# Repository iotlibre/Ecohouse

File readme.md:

# EcoHouse

Este kit de medida está pensado para tomar las medidas de consumo eléctrico de una vivienda o de un edificio con consumos inferiores a 10 KW. El sistema permite diferenciar varias zonas.

EcoHouse se puede instalar en el cuadro eléctrico principal o en cualquier otra parte  que nos permita tomar datos del consumo mediante pinzas (transformadores de intensidad). 

En el un edificio podemos tener tantos dispositivos como sean necesarios y el servidor EcoEficiencia los integrará en la misma instalación sin necesidad de configuraciones adicionales o cambios en el Firmware.

La comunicación se hace mediante Wifi por lo que no es necesario el cableado de datos al equipo solamente es necesario que esté dentro de la cobertura de la red WIFI del edificio. 

Para su uso no son necesarios conocimientos de informática aunque todos los desarrollos y el hardware están hechos bajo licencias libres lo que permite la modificación y mejora de las funcionalidades.

## Listado con las principales características
Las principales características de EcoBuilding son:
- 6 entradas para sensores de corriente con salida estandar de 50 mA o 1 Voltio
- Comunicación a Internet por WIFI local
- Configurable vía Web
- Display para mostrar el consumo instantáneo
- Alimentación a 220 voltios de corriente alterna
- Montaje en carril din
- Es posible configurar dos entradas analógicas adicionales pero en este caso el display permanecerá inoperativo
- La PCB integra un Arduino nano  con el ESP8266 12E
- Compatible con el [servidor de Open Energy Monitor](https://emoncms.org/)

## Montaje
El listado de componentes que has debido recibir es el siguientes:

- 1 PCB con los componentes de superficie ya montados
- 1 Carcasa para carril DIN
- 1 Tapa superior carcasa con display LCD 1602 y adaptador IIC/I2C
- 1 PCB Mesh building
- 1 Fuente de alimentación a 12 voltios
- 1 Arduino Nano
- 1 Integrado ESP8266 12E con el firmware mesh_building incluido
- 1 Convertidor DC-DC Step Down ajustable (salida 7,5V)
- 1 Regulador de tensión LM 1117
- 2 Conectores macho -hembra de 2.0mm para el ESP
- 2 Conectores macho hembra de 2.54mm para Arduino
- 2 Conectores macho hembra de 2.54mm para al display
- 9 Terminales de tornillo para PCB
- 2 Resistencias 10k 
- 3 Condensador 22uF
- 1 Condensador de 100nF
- 1 Diodo 1N4007

## Montaje
Partiendo de la PCB con los componentes de superficie soldar los componentes de menor a mayor tamaño por este orden:
- Resistencias
- Diodos
- Convertidor DC-DC Step Down ajustable (salida 7,5V)
- Conectores macho hembra de 2.0mm para el ESP
- Conectores macho hembra de 2.54mm para Arduino
- Conectores macho hembra de 2.54mm para al display
- Terminales de tornillo para PCB
- Condensador 22uF
- Condensador de 100nF
- Regulador de tensión LM 1117
 
Una vez esta completa la PCB insertar los integrados en sus posiciones
- Integrado ESP8266 12E
- Arduino Nano

Mirar la imagen para colocar los integrados de forma correcta, de otra maner no funcionarán y pueden sufrir daños

Por último conectar la tapa superior con el display a la PCB y montar la carcasa.

## Puesta a punto
La puesta a punto de libre_building consta de dos partes:
- El ajuste del voltaje de trabajo
- La configuración en la instalación

### El ajuste del voltaje de trabajo
El ajuste del voltaje de trabajo se hace para adaptar cualquier alimentación al voltaje de trabajo de EcoHouse que es 7,5 voltios.

La fuente de alimentación suministrada es de 12 voltios aunque el dispositivo funciona correctamente siempre que el voltaje de trabajo quede configurado entre 7 y 9 voltios.

Una vez conectada la  fuente de alimentación medir el voltaje en el punto (W103), situado al lado de  el Convertidor DC-DC (U1), y ajustarlo a 7,5 voltios con el potenciómetro que incorpora el convertidor. 

### La configuración en la instalación
En este punto se definen los parámetros del servidor de destino y la wifi local a la que va a estar conectado el dispositivo. Con este fin, la primera vez que se ponga en servicio el ESP y siempre que no encuentre la WIFI configurada, el ESP 8266 12E creará su propio punto de acceso, su propia red WIFI . Conectandose a cualquier dirección a través de este punto de acceso nos aparecerá la página de configuración del ESP. Tengase en cuenta que una  vez configurado el ESP y conectado a una red WIFI el router le asignará una única dirección IP a la que será necesario acceder para cambiar la configuración.

En caso de que se quiera actualizar el firmware del ESP a la última versión, este se puede encontrar en: [ecohouse-emonESP ](https://github.com/iotlibre/Ecohouse/tree/master/EmonESP)

### El firmware de Arduino
El firmware que que esta cargado por defecto en el arduino nano funciona correctamente sin embargo si quiere cambiar la configuración puedes encontrar la última actualización del firmware en este repositorio:[ecohouse-nano ](https://github.com/iotlibre/Ecohouse/tree/master/ecohouse-arduino_1)

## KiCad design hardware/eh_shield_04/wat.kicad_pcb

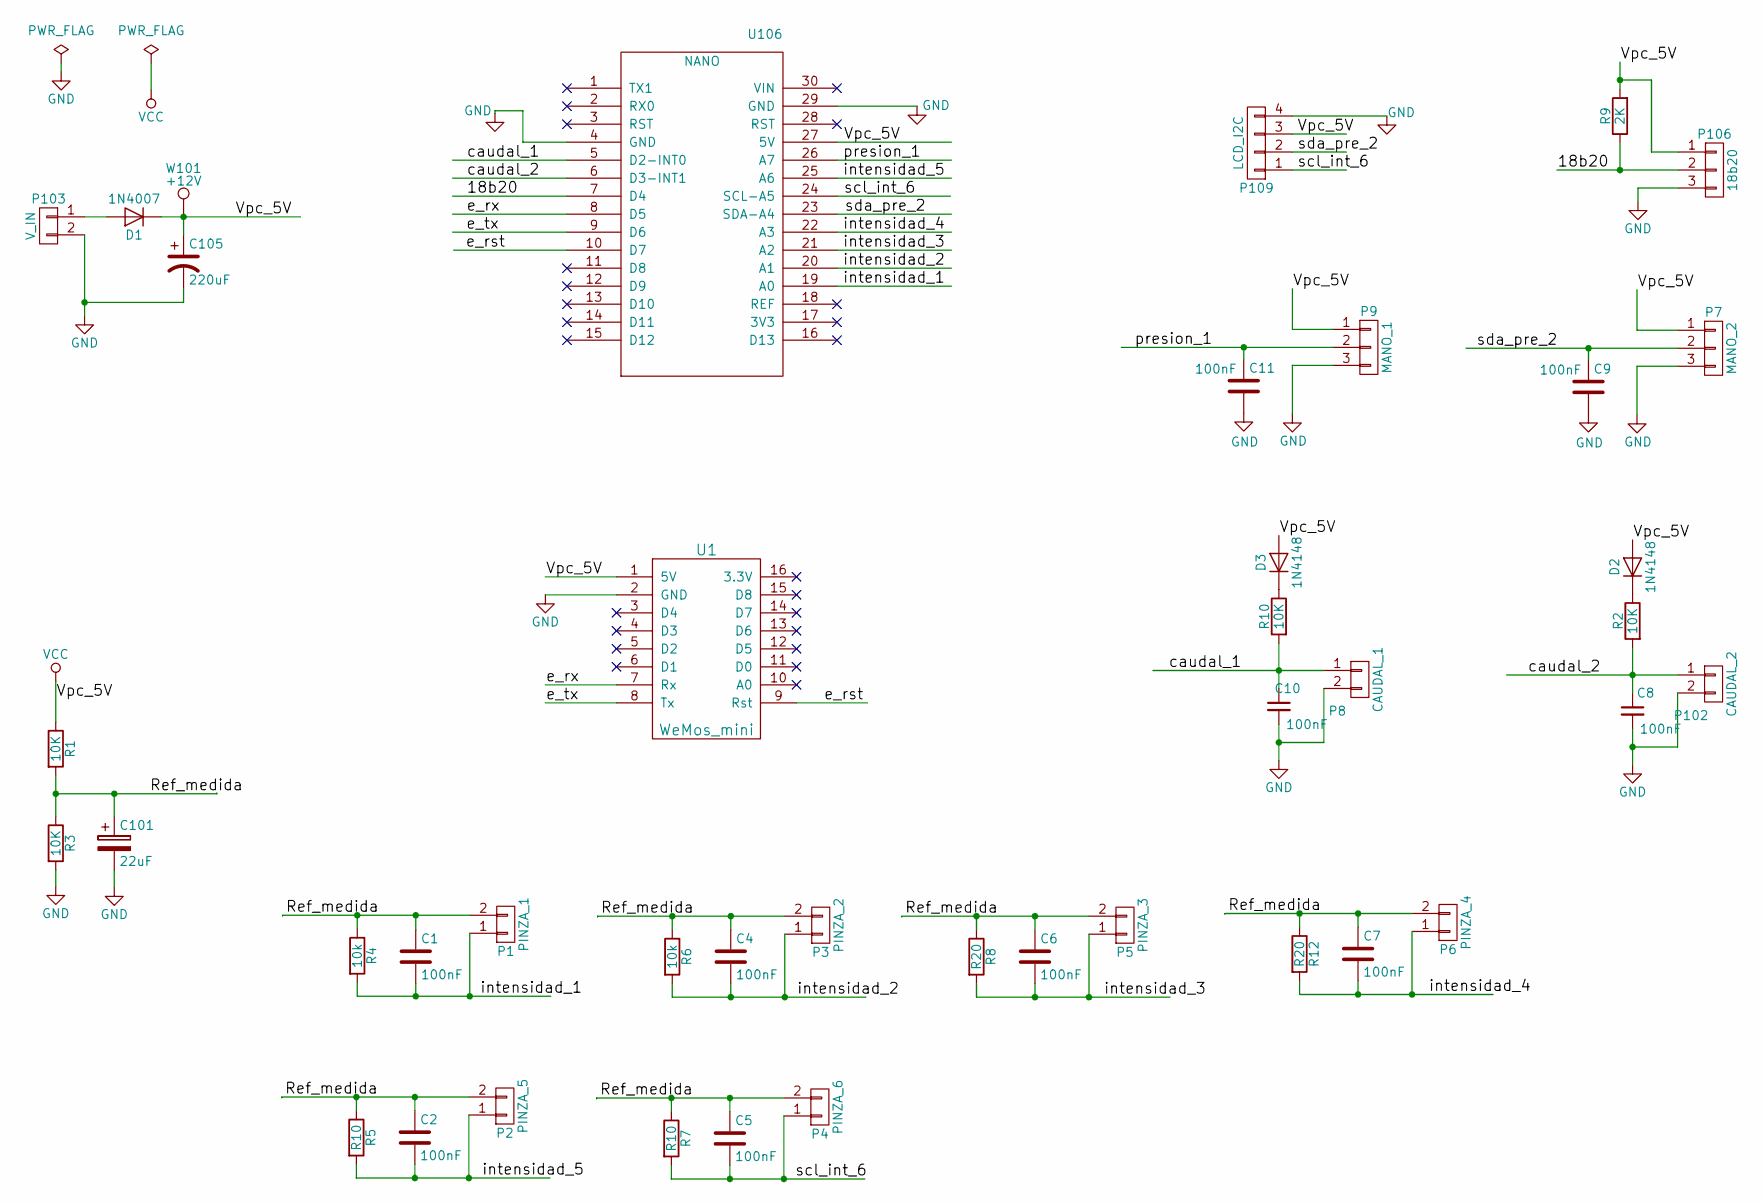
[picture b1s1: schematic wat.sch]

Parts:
C1, C2, C4, C5, C6, C7, C8, C9, C10, C11: 100nF; C_Disc_D5.0mm_W2.5mm_P5.00mm
C101: 22uF; CP_Radial_D5.0mm_P2.00mm
C105: 220uF; CP_Radial_D5.0mm_P2.00mm
D1: 1N4007; Diode_DO-35_SOD27_Horizontal_RM10
D2, D3: 1N4148; D_A-405_P7.62mm_Horizontal
P1: PINZA_1; bornier2
P2: PINZA_5; bornier2
P3: PINZA_2; bornier2
P4: PINZA_6; bornier2
P5: PINZA_3; bornier2
P6: PINZA_4; bornier2
P7: MANO_2; bornier3
P8: CAUDAL_1; bornier2
P9: MANO_1; bornier3
P102: CAUDAL_2; bornier2
P103: V_IN; bornier2
P106: 18b20; bornier3
P109: LCD_I2C; Pin_Header_Straight_1x04
R1, R2, R3, R10: 10K; Resistor_Horizontal_RM10mm
R4, R6: 10k; Resistor_Horizontal_RM10mm
R5, R7: R10; Resistor_Horizontal_RM10mm
R8, R12: R20; Resistor_Horizontal_RM10mm
R9: 2K; Resistor_Horizontal_RM10mm
U1: WeMos_mini; D1_mini_board_direct
U106: NANO; arduino_nano
W101: +12V; SolderWirePad_single_0-8mmDrill

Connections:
/18b20: P106.2, R9.1, U106.7 (D4)
/Ref_medida: C1.1, C2.1, C4.1, C5.1, C6.1, C7.1, C101.1, P1.2, P2.2, P3.2, P4.2, P5.2, P6.2, R1.2, R3.1, R4.1, R5.1, R6.1, R7.1, R8.1, R12.1
/caudal_1: C10.1, P8.1, R10.2, U106.5 (D2-INT0)
/caudal_2: C8.1, P102.1, R2.2, U106.6 (D3-INT1)
/e_rst: U1.9 (Rst), U106.10 (D7)
/e_rx: U1.7 (Rx), U106.8 (D5)
/e_tx: U1.8 (Tx), U106.9 (D6)
/intensidad_1: C1.2, P1.1, R4.2, U106.19 (A0)
/intensidad_2: C4.2, P3.1, R6.2, U106.20 (A1)
/intensidad_3: C6.2, P5.1, R8.2, U106.21 (A2)
/intensidad_4: C7.2, P6.1, R12.2, U106.22 (A3)
/intensidad_5: C2.2, P2.1, R5.2, U106.25 (A6)
/presion_1: C11.1, P9.2, U106.26 (A7)
/scl_int_6: C5.2, P4.1, P109.1, R7.2, U106.24 (SCL-A5)
/sda_pre_2: C9.1, P7.2, P109.2, U106.23 (SDA-A4)
GND: C8.2, C9.2, C10.2, C11.2, C101.2, C105.2, P7.3, P8.2, P9.3, P102.2, P103.2, P106.3, P109.4, R3.2, U1.2 (GND), U106.4 (GND), U106.29 (GND)
unnamed: D1.2 (A), P103.1
unnamed: D2.1 (K), R2.1
unnamed: D3.1 (K), R10.1
VCC: C105.1, D1.1 (K), D2.2 (A), D3.2 (A), P7.1, P9.1, P106.1, P109.3, R1.1, R9.2, U1.1 (5V), U106.27 (5V), W101.1

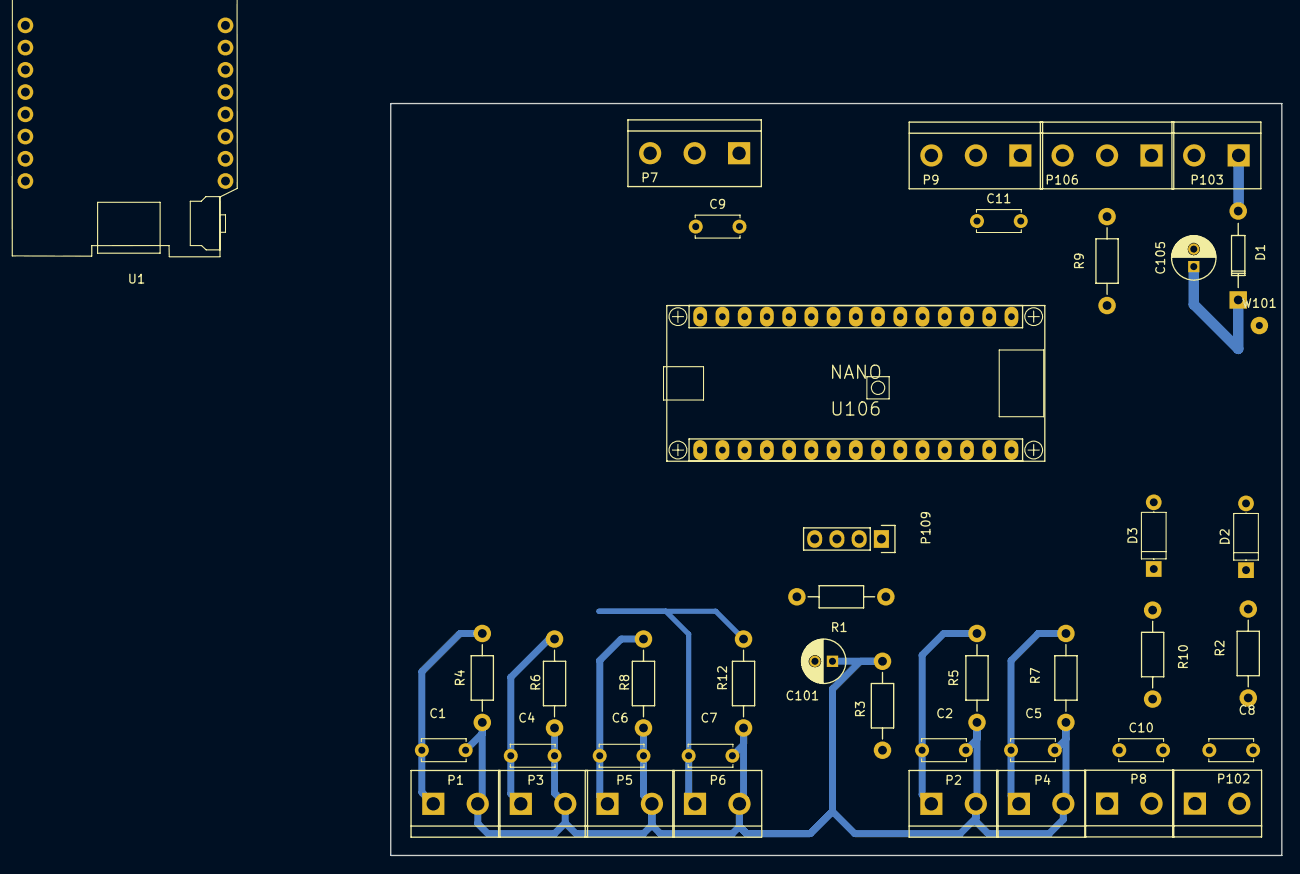
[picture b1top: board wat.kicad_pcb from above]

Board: 2 copper layers, 101.8 x 85.9 mm, 42 parts (0 on the bottom side), 20 nets.

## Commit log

2018-02-05 comit de inicio de ecohouse
2018-02-06 centro sociolaboral delicias
2018-02-07 cambio nombre comercial
2018-02-08 cambios hacia nueva version de PCB
2018-02-09 cambios hacia PCB con presion
2018-02-16 incluir fichero de mejoras
2018-02-23 hw wemos incluido
2018-03-23 inicio documentacion
2018-03-23 primera version completa
2018-03-23 cambio menor
2018-07-25 incluir descripcion e calculos
2018-08-07 alpedrete
2018-09-06 I2C direction for display
2018-10-03 tags
2019-06-13 20A without lcd
2019-08-28 sensibilidad en emonlib y eliminada la medida de temperatura
2019-09-20 plan de contingencia Adecuara
